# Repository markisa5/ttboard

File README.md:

# ttboard
*** test platform based on Teensy board

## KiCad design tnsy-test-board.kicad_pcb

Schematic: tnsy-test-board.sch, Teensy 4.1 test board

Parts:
C1: 4.7u; C_0603
C2: 100n; C_0603
C3, C4, C5, C6: 1u; C_0603
J1, J7: Conn_01x02; JST_EH_B02B-EH-A_02x2.50mm_Straight
J2, J3, J4: Conn_02x06_Odd_Even; JST_PUD_B12B-PUDSS_2x06x2.00mm_Straight
J5, J6, J27, J28, J29, J30, J31, J32: Conn_02x02_Odd_Even; JST_EH_B04B-EH-A_04x2.50mm_Straight
J8: Conn_02x08_Odd_Even; JST_PUD_B16B-PUDSS_2x08x2.00mm_Straight
R1, R2, R3, R4, R5, R6, R23, R33, R47, R57: 10k; R_0603
R7, R8, R9, R10, R11, R12, R13, R14, R15, R16, R17, R18, R19, R20, R21, R22, R24, R25, R26, R27, R29, R30, R31, R32, R34, R35, R36, R37, R39, R40, R41, R42, R43, R44, R45, R46, R49, R50, R51, R52, R53, R54, R55, R56, R59, R60, R61, R62, R336, R337: R; R_0603
R28, R38, R48, R58: 3.3k; R_0603
TH1, TH2, TH3, TH4: 2.2k; R_0603
U1: Teensy4.1; Teensy41
U2: ADS1015IDGS; TSSOP-10_3x3mm_Pitch0.5mm

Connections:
+5V: U1.48 (VIN); also elsewhere on the board
+24V: J7.2; also elsewhere on the board
/AO1_A0: R21.2, R22.1; also elsewhere on the board
/AO1_A1: R26.2, R27.1; also elsewhere on the board
/AO1_A2: R31.2, R32.1; also elsewhere on the board
/AO2_A0: R36.2, R37.1; also elsewhere on the board
/AO2_A1: R41.2, R42.1; also elsewhere on the board
/AO2_A2: R45.2, R46.1; also elsewhere on the board
/AO3_A0: R51.2, R52.1; also elsewhere on the board
/AO3_A1: R55.2, R56.1; also elsewhere on the board
/AO3_A2: R61.2, R62.1; also elsewhere on the board
/DI1_A0: R49.2, R50.1; also elsewhere on the board
/DI1_A1: R53.2, R54.1; also elsewhere on the board
/DI1_A2: R59.2, R60.1; also elsewhere on the board
/DIR1: U1.45 (23_A9_CRX1_MCLK1); also elsewhere on the board
/DIR2: U1.44 (22_A8_CTX1); also elsewhere on the board
/DIR3: U1.43 (21_A7_RX5_BCLK1); also elsewhere on the board
/DIR4: U1.42 (20_A6_TX5_LRCLK1); also elsewhere on the board
/DIR5: U1.37 (15_A1_RX3_SPDIF_IN); also elsewhere on the board
/DIR6: U1.36 (14_A0_TX3_SPDIF_OUT); also elsewhere on the board
/DIR7: U1.33 (41_A17); also elsewhere on the board
/DO1_A0: R19.2, R20.1; also elsewhere on the board
/DO1_A1: R24.2, R25.1; also elsewhere on the board
/DO1_A2: R29.2, R30.1; also elsewhere on the board
/DO2_A0: R34.2, R35.1; also elsewhere on the board
/DO2_A1: R39.2, R40.1; also elsewhere on the board
/DO2_A2: R43.2, R44.1; also elsewhere on the board
/DOUT1: J5.1; also elsewhere on the board
/DOUT2: J5.3; also elsewhere on the board
/DOUT3: J6.1; also elsewhere on the board
/DOUT4: J6.3; also elsewhere on the board
/DOUT5: J27.1; also elsewhere on the board
/DOUT6: J27.3; also elsewhere on the board
/DOUT7: J28.1; also elsewhere on the board
/DOUT8: J28.3; also elsewhere on the board
/DOUT9: J29.1; also elsewhere on the board
/DOUT10: J29.3; also elsewhere on the board
/DOUT11: J30.1; also elsewhere on the board
/DOUT12: J30.3; also elsewhere on the board
/DOUT13: J31.1; also elsewhere on the board
/DOUT14: J31.3; also elsewhere on the board
/DOUT15: J32.1; also elsewhere on the board
/DOUT16: J32.3; also elsewhere on the board
/DP1_A0: R9.2, R10.1; also elsewhere on the board
/DP1_A1: R7.2, R8.1; also elsewhere on the board
/DP2_A0: R13.2, R14.1; also elsewhere on the board
/DP2_A1: R11.2, R12.1; also elsewhere on the board
/DY_A0: R17.2, R18.1; also elsewhere on the board
/DY_A1: R15.2, R16.1; also elsewhere on the board
/DY_A2: R336.2, R337.1; also elsewhere on the board
/LED: U1.61 (LED); also elsewhere on the board
/MISO1: U1.14 (12_MISO_MQSL); also elsewhere on the board
/MISO2: U1.31 (39_MISO1_OUT1A); also elsewhere on the board
/MOSI1: U1.13 (11_MOSI_CTX1); also elsewhere on the board
/MOSI2: U1.18 (26_A12_MOSI1); also elsewhere on the board
/RX+: U1.60 (R+); also elsewhere on the board
/RX-: U1.65 (R-); also elsewhere on the board
/SCK1: U1.35 (13_SCK_LED); also elsewhere on the board
/SCK2: U1.19 (27_A13_SCK1); also elsewhere on the board
/SCL1: R6.2, U1.41 (19_A5_SCL); also elsewhere on the board
/SCL2: R4.2, U1.39 (17_A3_TX4_SDA1); also elsewhere on the board
/SCL3: R1.2, U1.16 (24_A10_TX6_SCL2), U2.9 (SDA)
/SDA1: R5.2, U1.40 (18_A4_SDA); also elsewhere on the board
/SDA2: R3.2, U1.38 (16_A2_RX4_SCL1); also elsewhere on the board
/SDA3: R2.2, U1.17 (25_A11_RX6_SDA2), U2.10 (SCL)
/T1: C3.1, R23.2, U2.4 (AIN0)
/T1A: J4.1; also elsewhere on the board
/T1B: J4.2; also elsewhere on the board
/T2: C4.1, R33.2, U2.5 (AIN1)
/T2A: J4.3; also elsewhere on the board
/T2B: J4.4; also elsewhere on the board
/T3: C5.1, R47.2, U2.6 (AIN2)
/T3A: J4.5; also elsewhere on the board
/T3B: J4.6; also elsewhere on the board
/T4: C6.1, R57.2, U2.7 (AIN3)
/T4A: J4.7; also elsewhere on the board
/T4B: J4.8; also elsewhere on the board
/T5A: J4.9; also elsewhere on the board
/T5B: J4.10; also elsewhere on the board
/T6A: J4.11; also elsewhere on the board
/T6B: J4.12; also elsewhere on the board
/TX+: U1.63 (T+); also elsewhere on the board
/TX-: U1.62 (T-); also elsewhere on the board
/VBAT: U1.50 (VBAT)
/VUSB: U1.49 (VUSB)
/analog-inputs-1/G1: J2.1; also elsewhere on the board
/analog-inputs-1/G2: J2.3; also elsewhere on the board
/analog-inputs-1/G3: J2.5; also elsewhere on the board
/analog-inputs-1/G4: J2.7; also elsewhere on the board
/analog-inputs-1/G5: J2.9; also elsewhere on the board
/analog-inputs-1/G6: J2.11; also elsewhere on the board
/analog-inputs-2/G1: J3.1; also elsewhere on the board
/analog-inputs-2/G2: J3.3; also elsewhere on the board
/analog-inputs-2/G3: J3.5; also elsewhere on the board
/analog-inputs-2/G4: J3.7; also elsewhere on the board
/analog-inputs-2/G5: J3.9; also elsewhere on the board
/analog-inputs-2/G6: J3.11; also elsewhere on the board
/digital-inputs/DIN1: J8.1; also elsewhere on the board
/digital-inputs/DIN2: J8.3; also elsewhere on the board
/digital-inputs/DIN3: J8.5; also elsewhere on the board
/digital-inputs/DIN4: J8.7; also elsewhere on the board
/digital-inputs/DIN5: J8.9; also elsewhere on the board
/digital-inputs/DIN6: J8.11; also elsewhere on the board
/digital-inputs/DIN7: J8.13; also elsewhere on the board
/digital-inputs/DIN8: J8.15; also elsewhere on the board
/~CS1~: U1.12 (10_CS_MQSR); also elsewhere on the board
/~CS2~: U1.30 (38_CS1_IN1); also elsewhere on the board
GND: C1.2, C2.2, C3.2, C4.2, C5.2, C6.2, J2.2, J2.4, J2.6, J2.8, J2.10, J2.12, J3.2, J3.4, J3.6, J3.8, J3.10, J3.12, J5.2, J5.4, J6.2, J6.4, J8.2, J8.4, J8.6, J8.8, J8.10, J8.12, J8.14, J8.16, J27.2, J27.4, J28.2, J28.4, J29.2, J29.4, J30.2, J30.4, J31.2, J31.4, J32.2, J32.4, R8.2, R10.2, R12.2, R14.2, R16.2, R18.2, R20.2, R22.2, R25.2, R27.2, R30.2, R32.2, R35.2, R37.2, R40.2, R42.2, R44.2, R46.2, R50.2, R52.2, R54.2, R56.2, R60.2, R62.2, R337.2, TH1.2, TH2.2, TH3.2, TH4.2, U1.1 (GND), U1.34 (GND), U1.47 (GND), U1.52 (GND), U1.64 (GND), U2.1 (ADDR), U2.3 (GND); also elsewhere on the board
GNDPWR: J1.1, J7.1; also elsewhere on the board
unnamed: R23.1, R28.2, TH1.1
unnamed: R33.1, R38.2, TH2.1
unnamed: R47.1, R48.2, TH3.1
unnamed: R57.1, R58.2, TH4.1
VDC: J1.2

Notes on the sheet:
ONBOARD TEMPERATURE
+ simulate gate source caps
+24V@3A
I2C
POTI SIMULATE TEMPERATURES x3 CHANNELS
8x DIGITAL OUTPUTS
OnBoard Display Device
SPI
ETHERNET EXTENSION BOARD
DIGITAL OUTPUTS
DIGITAL POTENTIOMETERS
ANALOG OUTPUTS
DISPLAY INTERFACE
POWER SUPPLY
ETHERNET EXPANSION
ANALOG INPUTS
DIGITAL INPUTS
I2C 3-bit address (3 devices)
I2C 3-bit address (2 devices)
I2C 2-bit address (2 devices)
SPI - 2 devices
I2C 2-bit address (1 device)
I2C 3-bit address (1 device)
8x ANALOG OUTPUTS
6x ANALOG INPUTS
8x DIGITAL INPUTS
I2C BUS 1
I2C BUS 2
6 SPARE
ADDRESS SELECTOR
DIGITAL POTI 1
DIGITAL POTI 2
DIGITAL OUT 1
DIGITAL OUT 2
DIGITAL IN 1
ANALOG OUT 1
ANALOG OUT 2
ANALOG OUT 3
DISPLAY
LEM current simulation

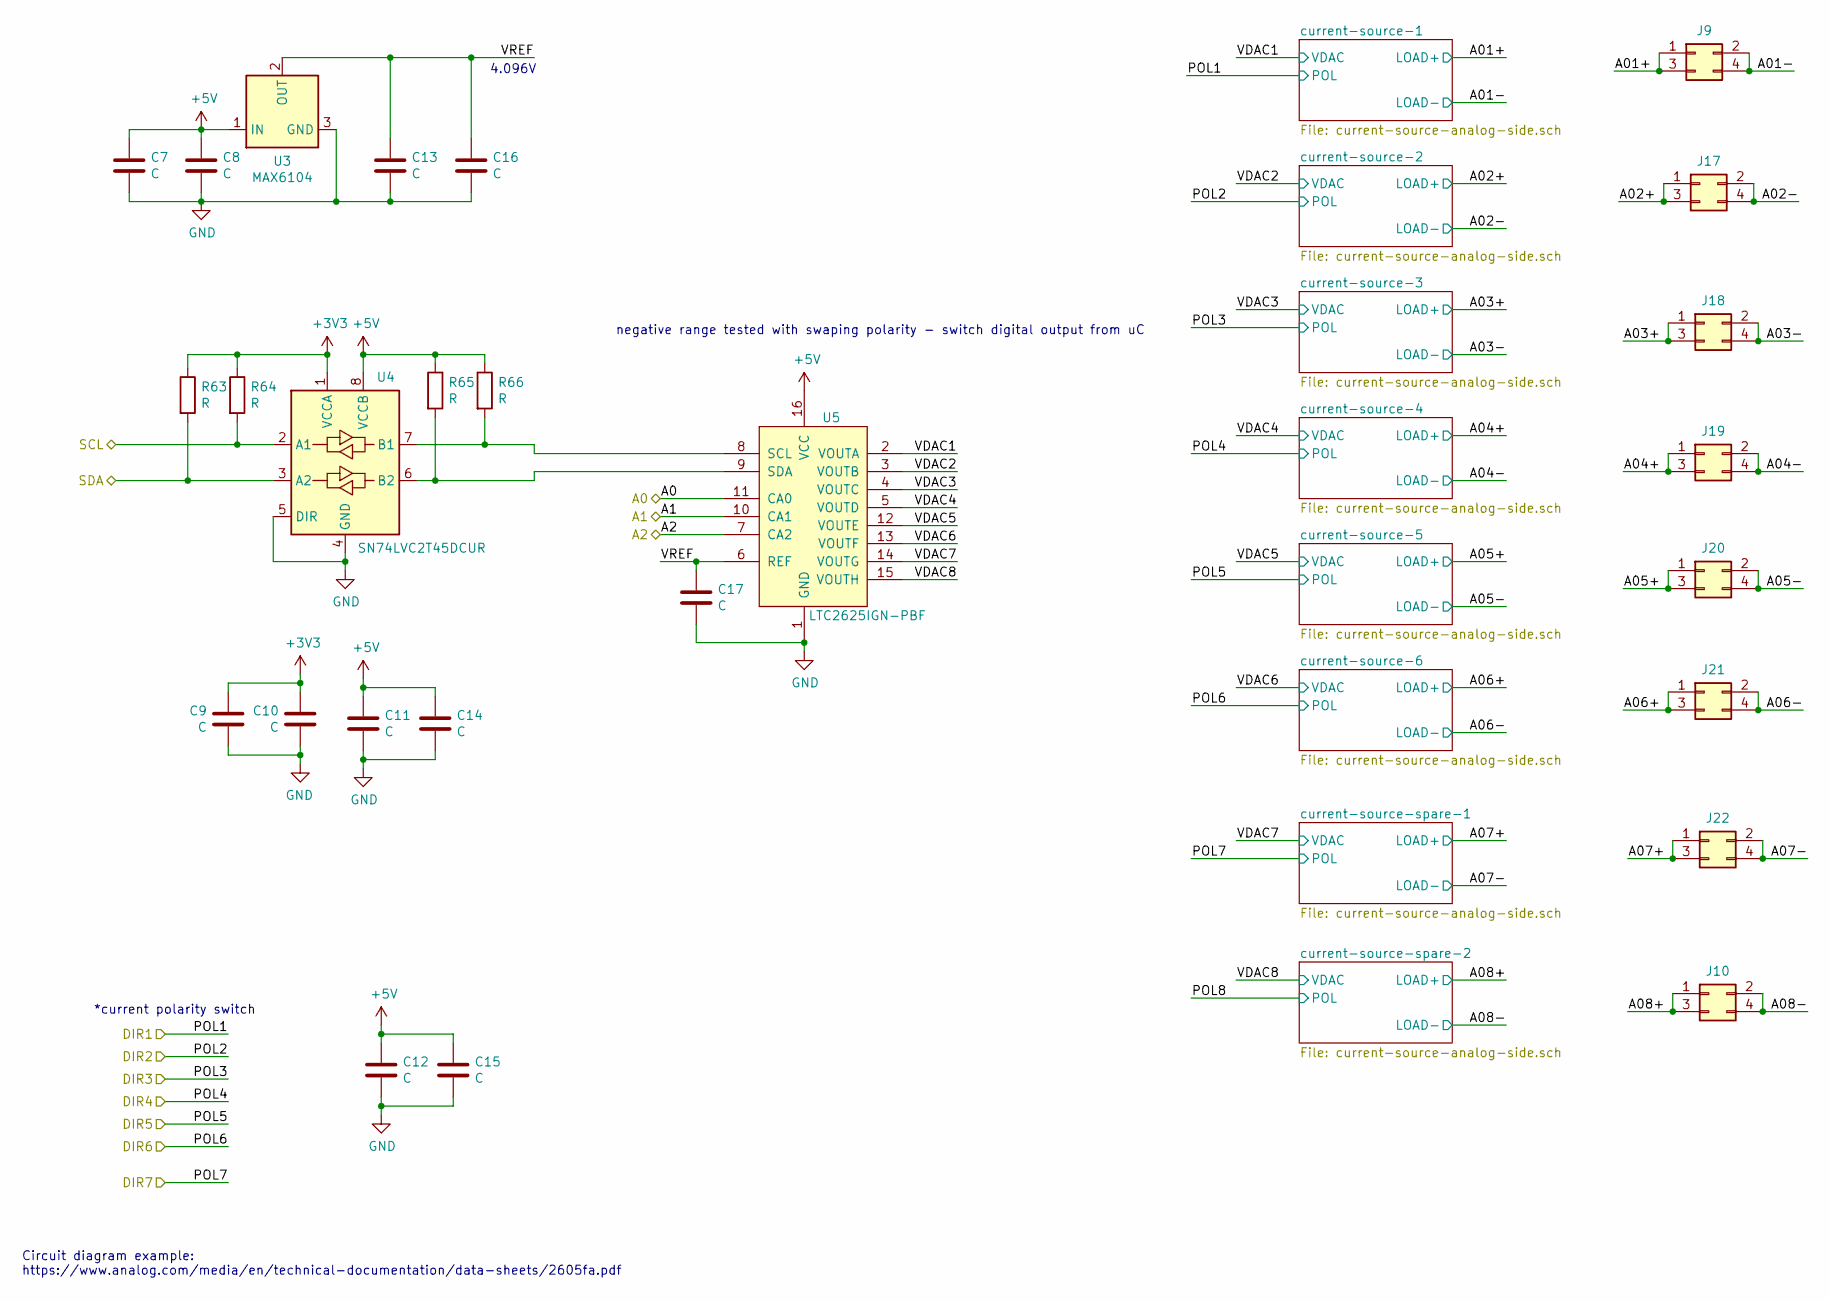
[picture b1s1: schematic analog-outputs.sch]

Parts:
C7, C8, C9, C10, C11, C12, C13, C14, C15, C16, C17: C; C_0603
J9, J10, J17, J18, J19, J20, J21, J22: Conn_02x02_Odd_Even; JST_EH_B04B-EH-A_04x2.50mm_Straight
R63, R64, R65, R66: R; R_0603
U3: MAX6104; SOT-23
U4: SN74LVC2T45DCUR; VSSOP-8_2.3x2mm_Pitch0.5mm
U5: LTC2625IGN-PBF; SSOP-16_3.9x4.9mm_Pitch0.635mm

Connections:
+5V: C7.1, C8.1, C11.1, C12.1, C14.1, C15.1, R65.1, R66.1, U3.1 (IN), U4.8 (VCCB), U5.16 (VCC); also elsewhere on the board
/AO1_A0: U5.11 (CA0); also elsewhere on the board
/AO1_A1: U5.10 (CA1); also elsewhere on the board
/AO1_A2: U5.7 (CA2); also elsewhere on the board
/SCL2: R63.2, U4.3 (A2); also elsewhere on the board
/SDA2: R64.2, U4.2 (A1); also elsewhere on the board
/analog-outputs-1/A01+: J9.1, J9.3; also elsewhere on the board
/analog-outputs-1/A01-: J9.2, J9.4; also elsewhere on the board
/analog-outputs-1/A02+: J17.1, J17.3; also elsewhere on the board
/analog-outputs-1/A02-: J17.2, J17.4; also elsewhere on the board
/analog-outputs-1/A03+: J18.1, J18.3; also elsewhere on the board
/analog-outputs-1/A03-: J18.2, J18.4; also elsewhere on the board
/analog-outputs-1/A04+: J19.1, J19.3; also elsewhere on the board
/analog-outputs-1/A04-: J19.2, J19.4; also elsewhere on the board
/analog-outputs-1/A05+: J20.1, J20.3; also elsewhere on the board
/analog-outputs-1/A05-: J20.2, J20.4; also elsewhere on the board
/analog-outputs-1/A06+: J21.1, J21.3; also elsewhere on the board
/analog-outputs-1/A06-: J21.2, J21.4; also elsewhere on the board
/analog-outputs-1/A07+: J22.1, J22.3; also elsewhere on the board
/analog-outputs-1/A07-: J22.2, J22.4; also elsewhere on the board
/analog-outputs-1/A08+: J10.1, J10.3; also elsewhere on the board
/analog-outputs-1/A08-: J10.2, J10.4; also elsewhere on the board
/analog-outputs-1/VDAC1: U5.2 (VOUTA); also elsewhere on the board
/analog-outputs-1/VDAC2: U5.3 (VOUTB); also elsewhere on the board
/analog-outputs-1/VDAC3: U5.4 (VOUTC); also elsewhere on the board
/analog-outputs-1/VDAC4: U5.5 (VOUTD); also elsewhere on the board
/analog-outputs-1/VDAC5: U5.12 (VOUTE); also elsewhere on the board
/analog-outputs-1/VDAC6: U5.13 (VOUTF); also elsewhere on the board
/analog-outputs-1/VDAC7: U5.14 (VOUTG); also elsewhere on the board
/analog-outputs-1/VDAC8: U5.15 (VOUTH); also elsewhere on the board
/analog-outputs-1/VREF: C13.1, C16.1, C17.1, U3.2 (OUT), U5.6 (REF)
GND: C7.2, C8.2, C9.2, C10.2, C11.2, C12.2, C13.2, C14.2, C15.2, C16.2, C17.2, U3.3 (GND), U4.4 (GND), U4.5 (DIR), U5.1 (GND); also elsewhere on the board
unnamed: R65.2, U4.6 (B2), U5.9 (SDA)
unnamed: R66.2, U4.7 (B1), U5.8 (SCL)

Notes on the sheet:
Circuit diagram example: https://www.analog.com/media/en/technical-documentation/data-sheets/2605fa.pdf
negative range tested with swaping polarity - switch digital output from uC
*current polarity switch
4.096V

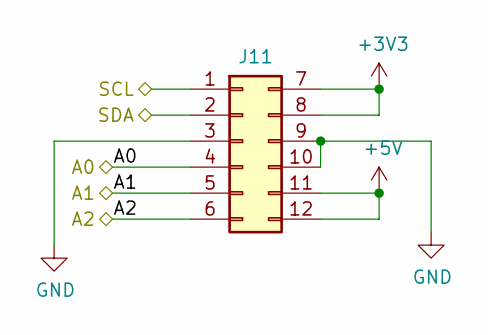
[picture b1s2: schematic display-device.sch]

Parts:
J11: Conn_02x06_Top_Bottom; JST_PUD_B12B-PUDSS_2x06x2.00mm_Straight

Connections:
+5V: J11.11, J11.12; also elsewhere on the board
/DY_A0: J11.4; also elsewhere on the board
/DY_A1: J11.5; also elsewhere on the board
/DY_A2: J11.6; also elsewhere on the board
/SCL1: J11.1; also elsewhere on the board
/SDA1: J11.2; also elsewhere on the board
GND: J11.3, J11.9, J11.10; also elsewhere on the board

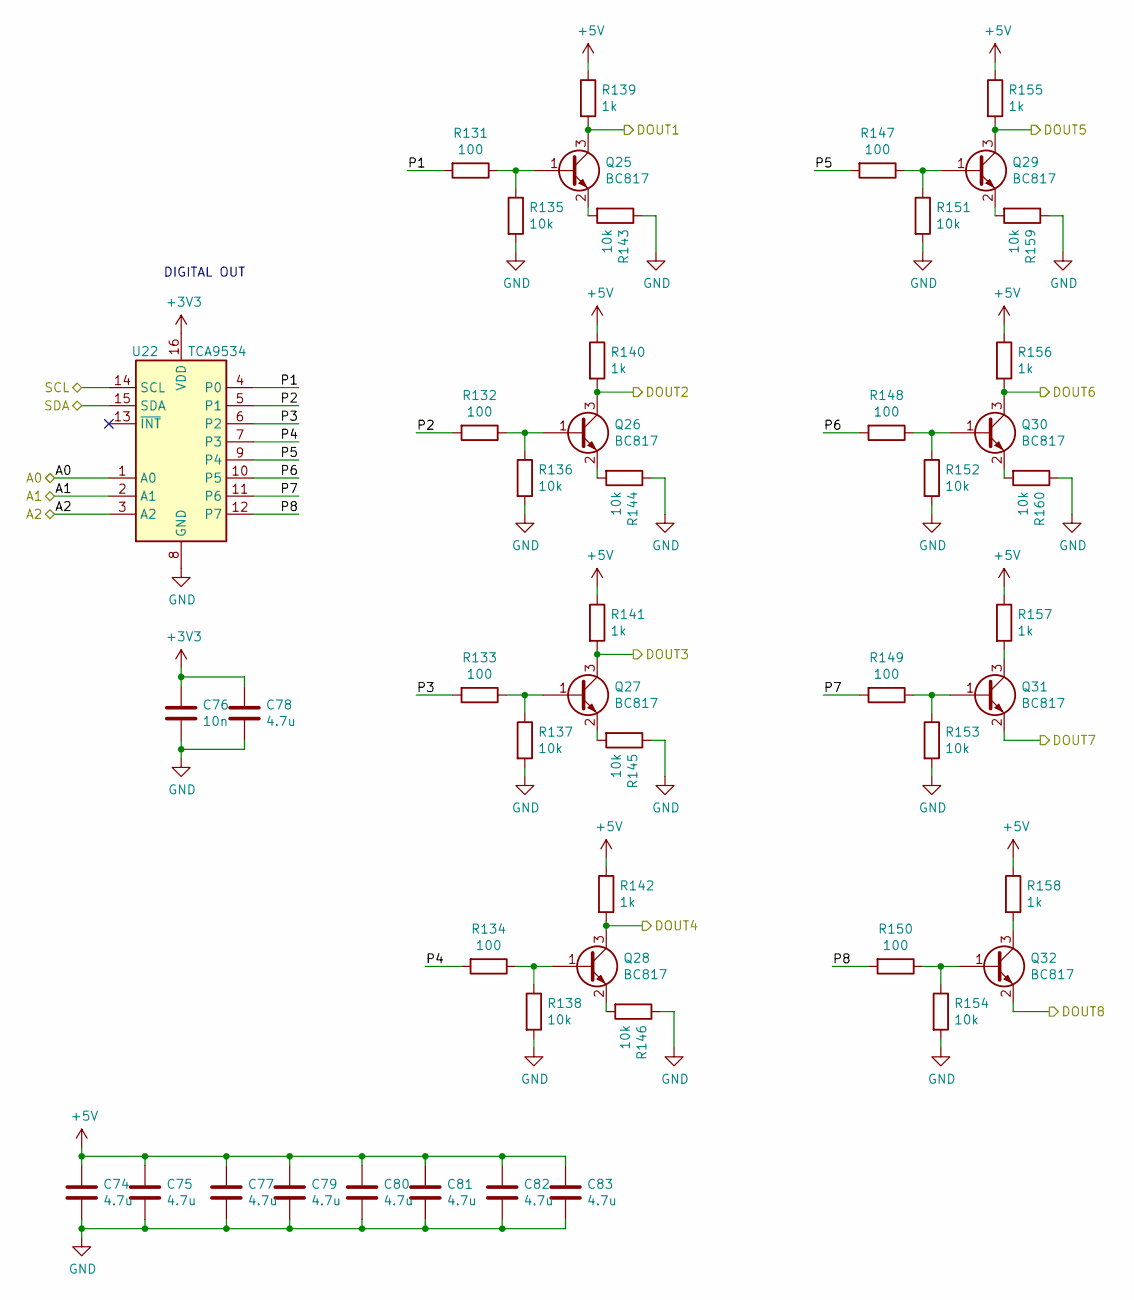
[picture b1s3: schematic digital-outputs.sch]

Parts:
C74, C75, C77, C78, C79, C80, C81, C82, C83: 4.7u; C_0603
C76: 10n; C_0603
Q25, Q26, Q27, Q28, Q29, Q30, Q31, Q32: BC817; SOT-23
R131, R132, R133, R134, R147, R148, R149, R150: 100; R_0603
R135, R136, R137, R138, R143, R144, R145, R146, R151, R152, R153, R154, R159, R160: 10k; R_0603
R139, R140, R141, R142, R155, R156, R157, R158: 1k; R_0603
U22: TCA9534; TSSOP-16_4.4x5mm_Pitch0.65mm

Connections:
+5V: C74.1, C75.1, C77.1, C79.1, C80.1, C81.1, C82.1, C83.1, R139.1, R140.1, R141.1, R142.1, R155.1, R156.1, R157.1, R158.1; also elsewhere on the board
/DO1_A0: U22.1 (A0); also elsewhere on the board
/DO1_A1: U22.2 (A1); also elsewhere on the board
/DO1_A2: U22.3 (A2); also elsewhere on the board
/DOUT1: Q25.3 (C), R139.2; also elsewhere on the board
/DOUT2: Q26.3 (C), R140.2; also elsewhere on the board
/DOUT3: Q27.3 (C), R141.2; also elsewhere on the board
/DOUT4: Q28.3 (C), R142.2; also elsewhere on the board
/DOUT5: Q29.3 (C), R155.2; also elsewhere on the board
/DOUT6: Q30.3 (C), R156.2; also elsewhere on the board
/DOUT7: Q31.2 (E); also elsewhere on the board
/DOUT8: Q32.2 (E); also elsewhere on the board
/SCL2: U22.14 (SCL); also elsewhere on the board
/SDA2: U22.15 (SDA); also elsewhere on the board
/digital-outputs-1/P1: R131.2, U22.4 (P0)
/digital-outputs-1/P2: R132.2, U22.5 (P1)
/digital-outputs-1/P3: R133.2, U22.6 (P2)
/digital-outputs-1/P4: R134.2, U22.7 (P3)
/digital-outputs-1/P5: R147.2, U22.9 (P4)
/digital-outputs-1/P6: R148.2, U22.10 (P5)
/digital-outputs-1/P7: R149.2, U22.11 (P6)
/digital-outputs-1/P8: R150.2, U22.12 (P7)
GND: C74.2, C75.2, C76.2, C77.2, C78.2, C79.2, C80.2, C81.2, C82.2, C83.2, R135.2, R136.2, R137.2, R138.2, R143.1, R144.1, R145.1, R146.1, R151.2, R152.2, R153.2, R154.2, R159.1, R160.1, U22.8 (GND); also elsewhere on the board
unnamed: Q25.1 (B), R131.1, R135.1
unnamed: Q25.2 (E), R143.2
unnamed: Q26.1 (B), R132.1, R136.1
unnamed: Q26.2 (E), R144.2
unnamed: Q27.1 (B), R133.1, R137.1
unnamed: Q27.2 (E), R145.2
unnamed: Q28.1 (B), R134.1, R138.1
unnamed: Q28.2 (E), R146.2
unnamed: Q29.1 (B), R147.1, R151.1
unnamed: Q29.2 (E), R159.2
unnamed: Q30.1 (B), R148.1, R152.1
unnamed: Q30.2 (E), R160.2
unnamed: Q31.1 (B), R149.1, R153.1
unnamed: Q31.3 (C), R157.2
unnamed: Q32.1 (B), R150.1, R154.1
unnamed: Q32.3 (C), R158.2

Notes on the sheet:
DIGITAL OUT

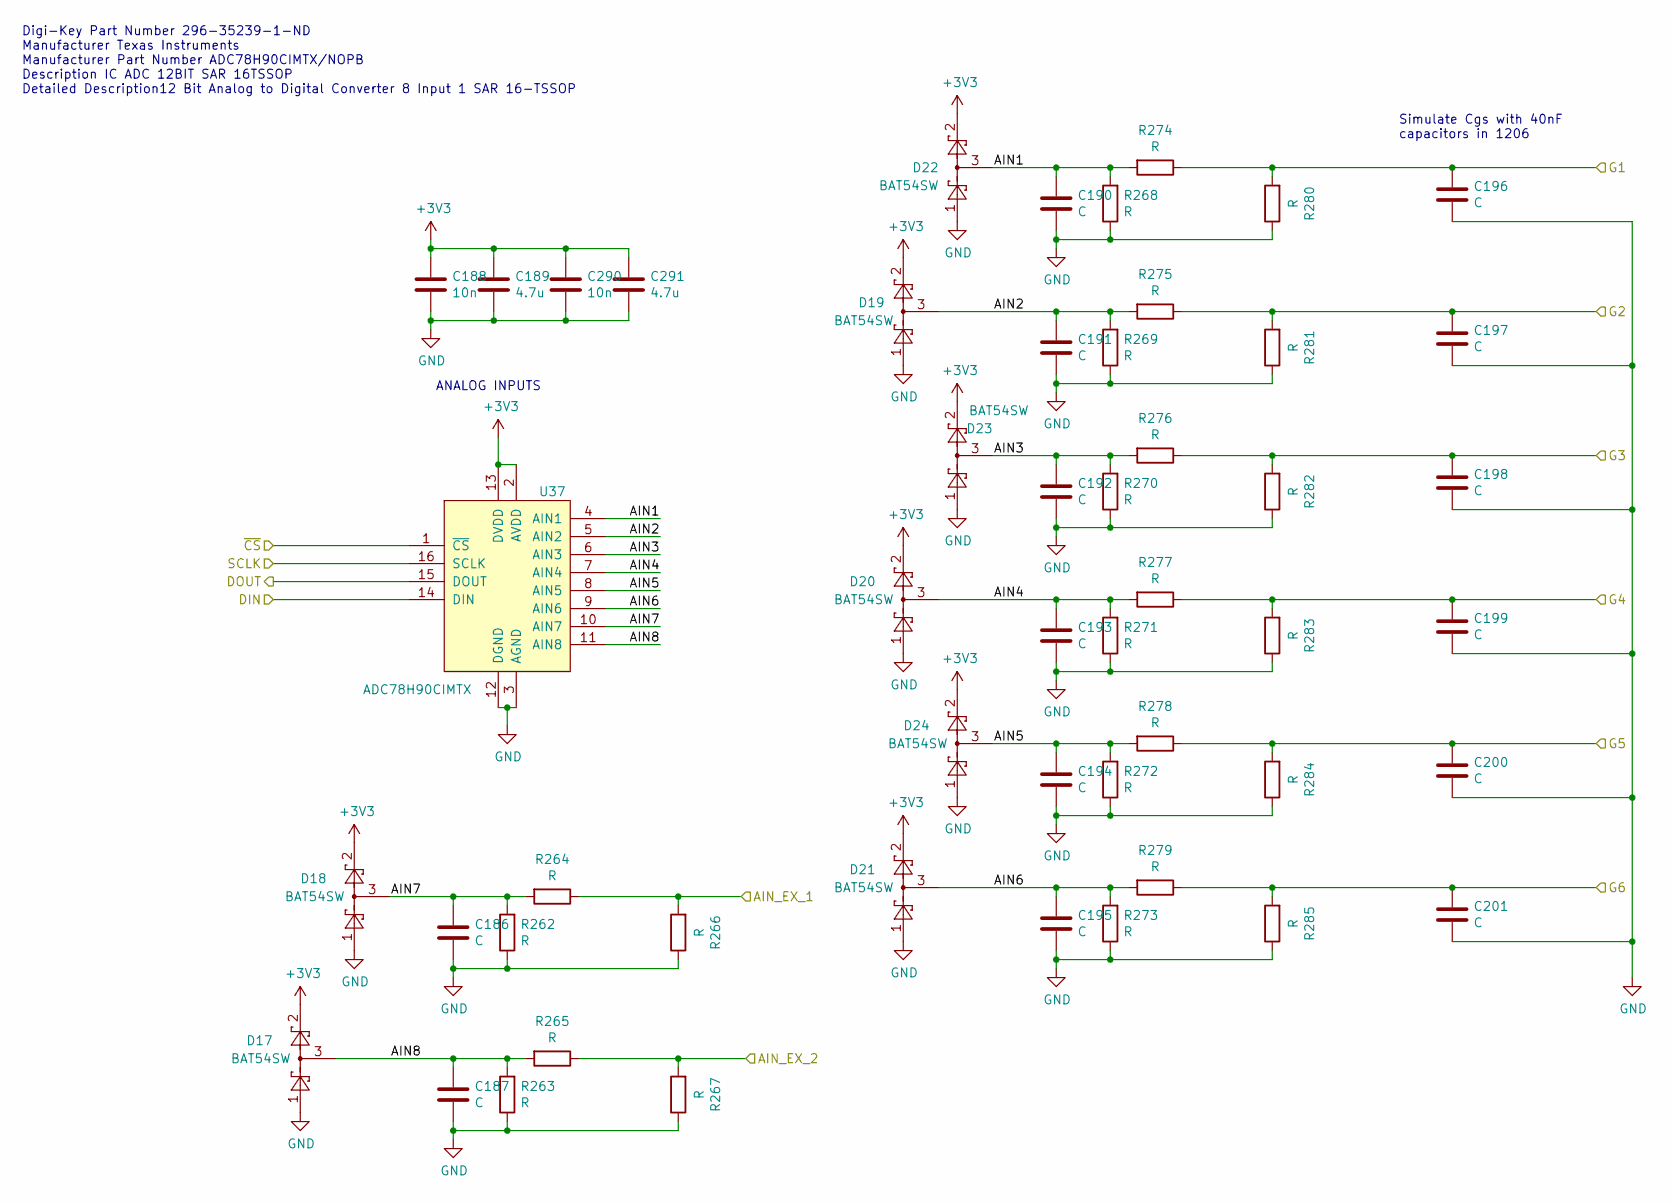
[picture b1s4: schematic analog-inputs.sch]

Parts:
C86, C288: 10n; C_0603
C87, C289: 4.7u; C_0603
C186, C187, C190, C191, C192, C193, C194, C195: C; C_0603
C196, C197, C198, C199, C200, C201: C; C_1206
D1, D2, D3, D4, D5, D6, D7, D8: BAT54SW; SOT-323_SC-70_Handsoldering
R262, R263, R264, R265, R268, R269, R270, R271, R272, R273, R274, R275, R276, R277, R278, R279: R; R_0603
R266, R267, R280, R281, R282, R283, R284, R285: R; R_0805
U37: ADC78H90CIMTX; TSSOP-16_4.4x5mm_Pitch0.65mm

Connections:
/AIN_3V3: R264.1, R266.2
/AIN_5V: R265.1, R267.2
/MISO1: U37.15 (DOUT); also elsewhere on the board
/MOSI1: U37.14 (DIN); also elsewhere on the board
/SCK1: U37.16 (SCLK); also elsewhere on the board
/analog-inputs-1/G1: C196.1, R274.1, R280.2; also elsewhere on the board
/analog-inputs-1/G2: C197.1, R275.1, R281.2; also elsewhere on the board
/analog-inputs-1/G3: C198.1, R276.1, R282.2; also elsewhere on the board
/analog-inputs-1/G4: C199.1, R277.1, R283.2; also elsewhere on the board
/analog-inputs-1/G5: C200.1, R278.1, R284.2; also elsewhere on the board
/analog-inputs-1/G6: C201.1, R279.1, R285.2; also elsewhere on the board
/~CS1~: U37.1 (~CS~); also elsewhere on the board
GND: C86.2, C87.2, C186.2, C187.2, C190.2, C191.2, C192.2, C193.2, C194.2, C195.2, C196.2, C197.2, C198.2, C199.2, C200.2, C201.2, C288.2, C289.2, D1.1, D2.1, D3.1, D4.1, D5.1, D6.1, D7.1, D8.1, R262.1, R263.1, R266.1, R267.1, R268.1, R269.1, R270.1, R271.1, R272.1, R273.1, R280.1, R281.1, R282.1, R283.1, R284.1, R285.1, U37.3 (AGND), U37.12 (DGND); also elsewhere on the board

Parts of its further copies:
C84, C85, C88, C89, C90, C91, C92, C93: C; C_0603
C94, C95, C96, C97, C98, C99: C; C_1206
C188, C290: 10n; C_0603
C189, C291: 4.7u; C_0603
D17, D18, D19, D20, D21, D22, D23, D24: BAT54SW; SOT-323_SC-70_Handsoldering
R161, R162, R163, R164, R167, R168, R169, R170, R171, R172, R173, R174, R175, R176, R177, R178: R; R_0603
R165, R166, R179, R180, R181, R182, R183, R184: R; R_0805
U23: ADC78H90CIMTX; TSSOP-16_4.4x5mm_Pitch0.65mm

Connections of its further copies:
/AIN_12V: R163.1, R165.2
/AIN_24V: R164.1, R166.2
/MISO2: U23.15 (DOUT); also elsewhere on the board
/MOSI2: U23.14 (DIN); also elsewhere on the board
/SCK2: U23.16 (SCLK); also elsewhere on the board
/analog-inputs-2/G1: C94.1, R173.1, R179.2; also elsewhere on the board
/analog-inputs-2/G2: C95.1, R174.1, R180.2; also elsewhere on the board
/analog-inputs-2/G3: C96.1, R175.1, R181.2; also elsewhere on the board
/analog-inputs-2/G4: C97.1, R176.1, R182.2; also elsewhere on the board
/analog-inputs-2/G5: C98.1, R177.1, R183.2; also elsewhere on the board
/analog-inputs-2/G6: C99.1, R178.1, R184.2; also elsewhere on the board
/~CS2~: U23.1 (~CS~); also elsewhere on the board
GND: C84.2, C85.2, C88.2, C89.2, C90.2, C91.2, C92.2, C93.2, C94.2, C95.2, C96.2, C97.2, C98.2, C99.2, C188.2, C189.2, C290.2, C291.2, D17.1, D18.1, D19.1, D20.1, D21.1, D22.1, D23.1, D24.1, R161.1, R162.1, R165.1, R166.1, R167.1, R168.1, R169.1, R170.1, R171.1, R172.1, R179.1, R180.1, R181.1, R182.1, R183.1, R184.1, U23.3 (AGND), U23.12 (DGND); also elsewhere on the board

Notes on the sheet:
ANALOG INPUTS
Digi-Key Part Number 296-35239-1-ND Manufacturer Texas Instruments Manufacturer Part Number ADC78H90CIMTX/NOPB Description IC ADC 12BIT SAR 16TSSOP Detailed Description12 Bit Analog to Digital Converter 8 Input 1 SAR 16-TSSOP
Simulate Cgs with 40nF capacitors in 1206

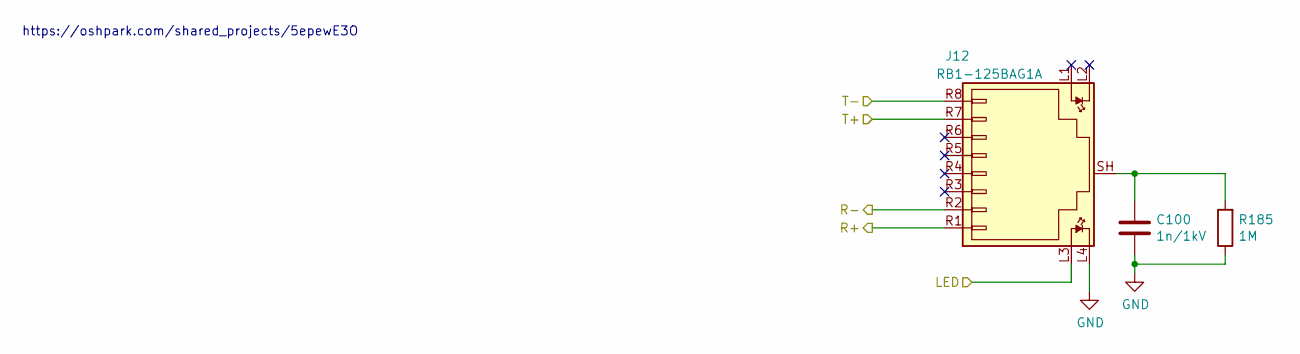
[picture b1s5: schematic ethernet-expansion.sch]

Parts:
C100: 1n/1kV; C_0603
J12: RB1-125BAG1A; RJ45_Female_RB1-125BAG1A; MPN RB1-125BAG1A; Digi-Key_PN 1278-1011-ND
R185: 1M; R_0805

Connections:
/LED: J12.L3; also elsewhere on the board
/RX+: J12.R1; also elsewhere on the board
/RX-: J12.R2; also elsewhere on the board
/TX+: J12.R7; also elsewhere on the board
/TX-: J12.R8; also elsewhere on the board
GND: C100.2, J12.L4, R185.1; also elsewhere on the board
unnamed: C100.1, J12.SH, R185.2

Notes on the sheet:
https://oshpark.com/shared_projects/5epewE3O

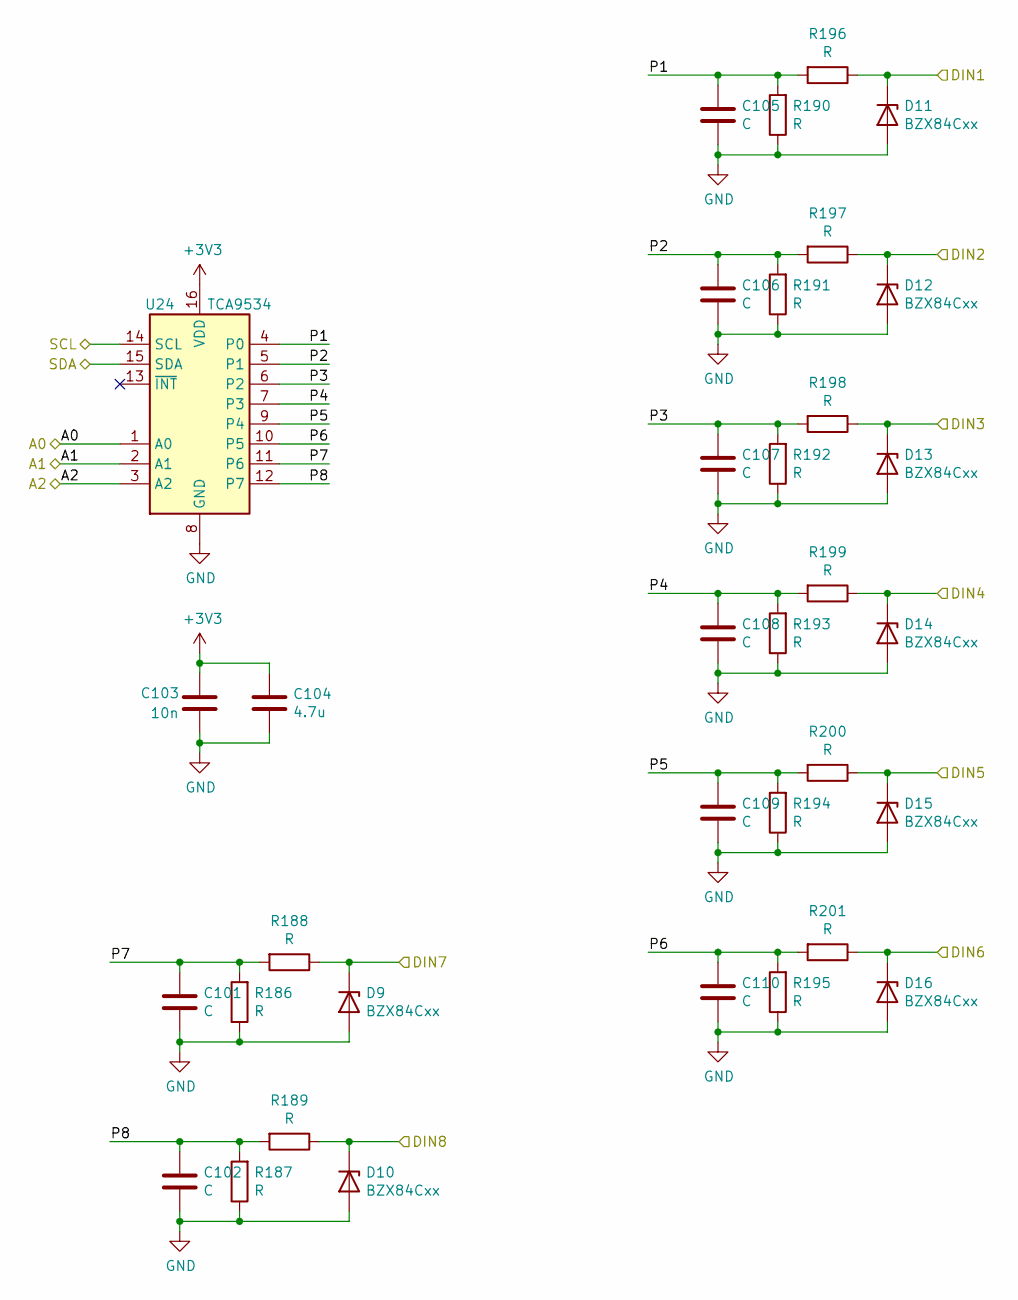
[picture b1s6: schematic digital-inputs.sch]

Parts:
C101, C102, C105, C106, C107, C108, C109, C110: C; C_0603
C103: 10n; C_0603
C104: 4.7u; C_0603
D9, D10, D11, D12, D13, D14, D15, D16: BZX84Cxx; D_SOT-23_ANK
R186, R187, R188, R189, R190, R191, R192, R193, R194, R195, R196, R197, R198, R199, R200, R201: R; R_0603
U24: TCA9534; TSSOP-16_4.4x5mm_Pitch0.65mm

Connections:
/DI1_A0: U24.1 (A0); also elsewhere on the board
/DI1_A1: U24.2 (A1); also elsewhere on the board
/DI1_A2: U24.3 (A2); also elsewhere on the board
/SCL2: U24.14 (SCL); also elsewhere on the board
/SDA2: U24.15 (SDA); also elsewhere on the board
/digital-inputs/DIN1: D11.1 (K), R196.1; also elsewhere on the board
/digital-inputs/DIN2: D12.1 (K), R197.1; also elsewhere on the board
/digital-inputs/DIN3: D13.1 (K), R198.1; also elsewhere on the board
/digital-inputs/DIN4: D14.1 (K), R199.1; also elsewhere on the board
/digital-inputs/DIN5: D15.1 (K), R200.1; also elsewhere on the board
/digital-inputs/DIN6: D16.1 (K), R201.1; also elsewhere on the board
/digital-inputs/DIN7: D9.1 (K), R188.1; also elsewhere on the board
/digital-inputs/DIN8: D10.1 (K), R189.1; also elsewhere on the board
/digital-inputs/P1: C105.1, R190.2, R196.2, U24.4 (P0)
/digital-inputs/P2: C106.1, R191.2, R197.2, U24.5 (P1)
/digital-inputs/P3: C107.1, R192.2, R198.2, U24.6 (P2)
/digital-inputs/P4: C108.1, R193.2, R199.2, U24.7 (P3)
/digital-inputs/P5: C109.1, R194.2, R200.2, U24.9 (P4)
/digital-inputs/P6: C110.1, R195.2, R201.2, U24.10 (P5)
/digital-inputs/P7: C101.1, R186.2, R188.2, U24.11 (P6)
/digital-inputs/P8: C102.1, R187.2, R189.2, U24.12 (P7)
GND: C101.2, C102.2, C103.2, C104.2, C105.2, C106.2, C107.2, C108.2, C109.2, C110.2, D9.2 (A), D10.2 (A), D11.2 (A), D12.2 (A), D13.2 (A), D14.2 (A), D15.2 (A), D16.2 (A), R186.1, R187.1, R190.1, R191.1, R192.1, R193.1, R194.1, R195.1, U24.8 (GND); also elsewhere on the board

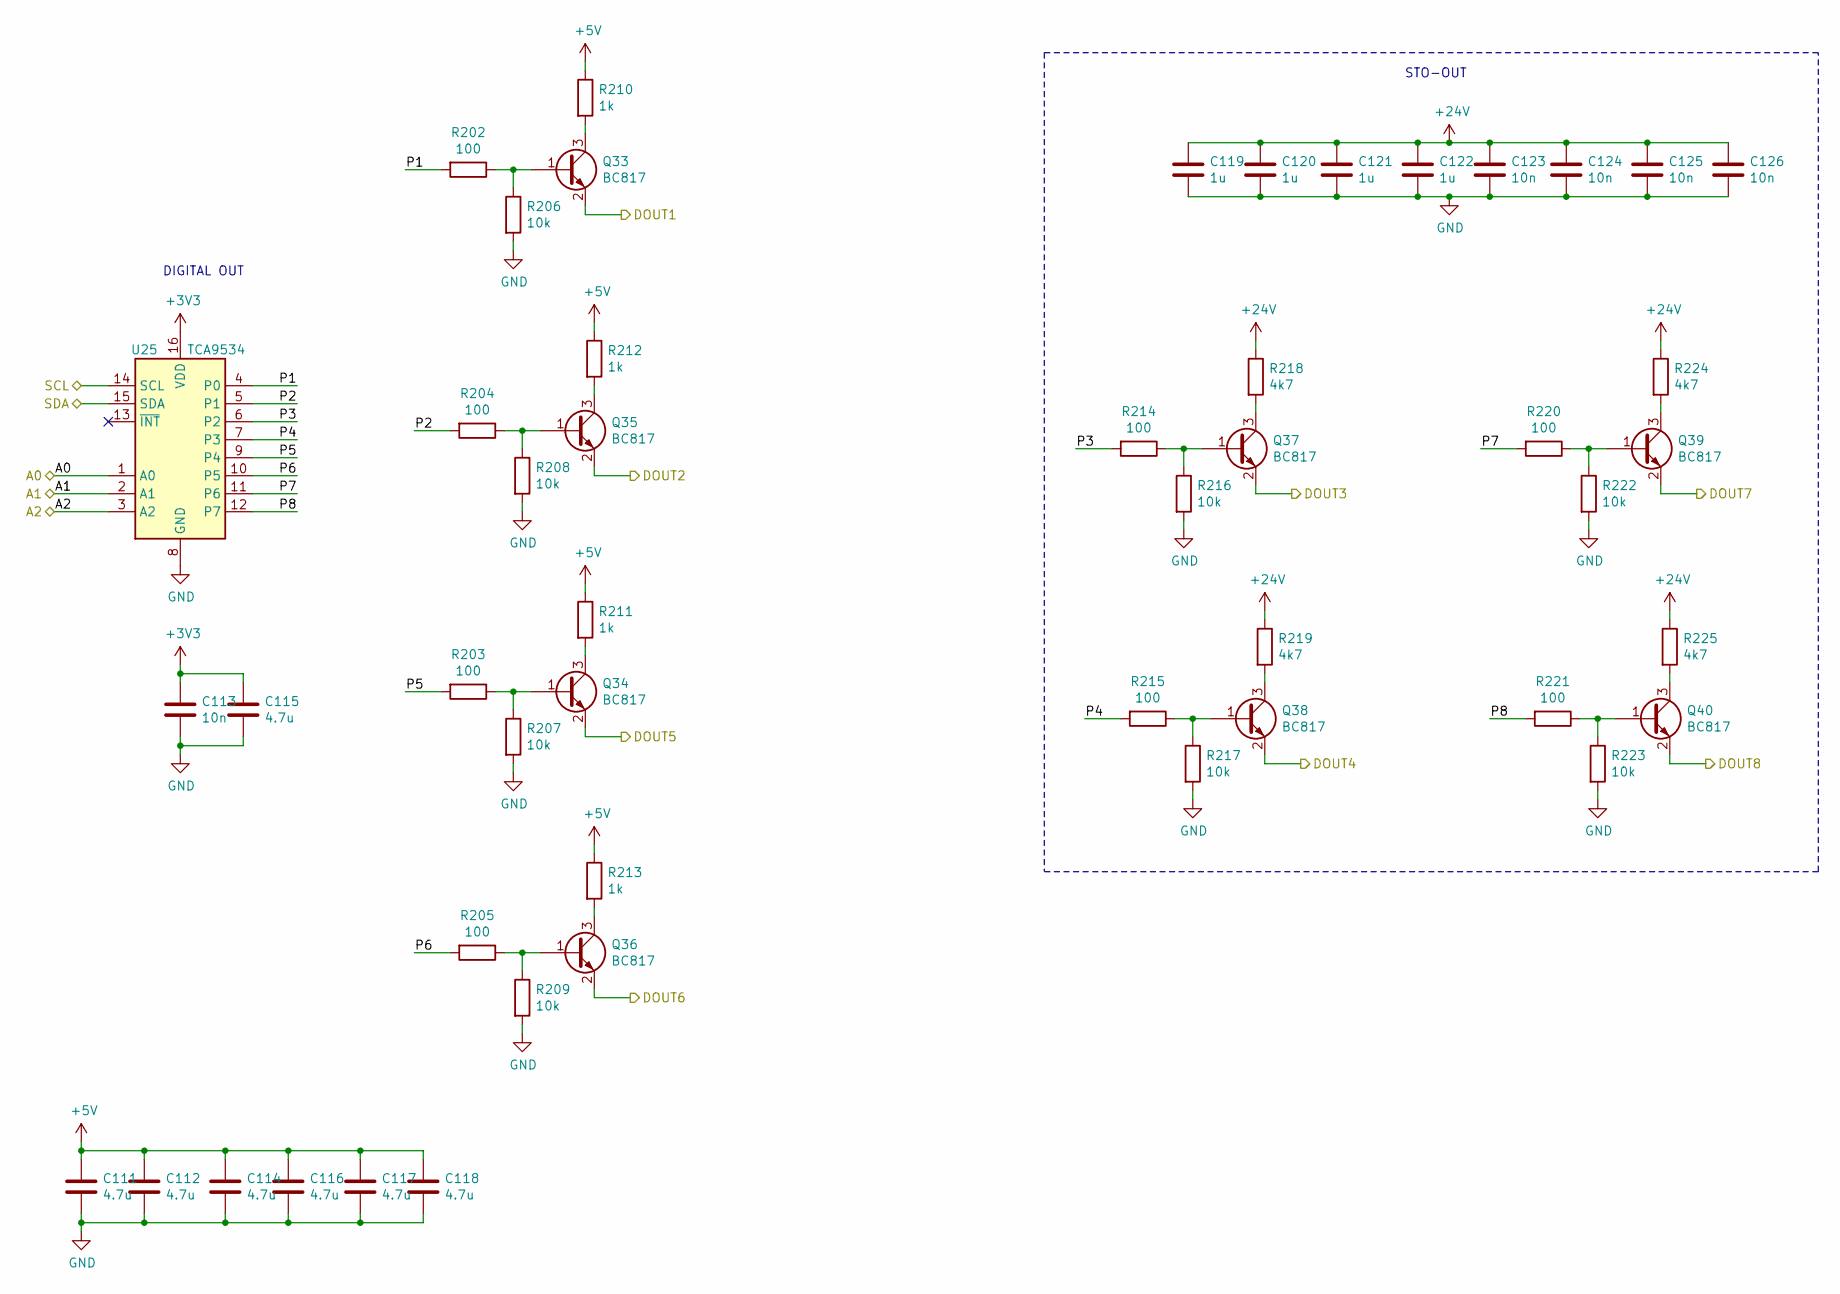
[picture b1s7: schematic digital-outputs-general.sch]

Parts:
C111, C112, C114, C115, C116, C117, C118: 4.7u; C_0603
C113, C123, C124, C125, C126: 10n; C_0603
C119, C120, C121, C122: 1u; C_0603
Q33, Q34, Q35, Q36, Q37, Q38, Q39, Q40: BC817; SOT-23
R202, R203, R204, R205, R214, R215, R220, R221: 100; R_0603
R206, R207, R208, R209, R216, R217, R222, R223: 10k; R_0603
R210, R211, R212, R213: 1k; R_0603
R218, R219, R224, R225: 4k7; R_0603
U25: TCA9534; TSSOP-16_4.4x5mm_Pitch0.65mm

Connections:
+5V: C111.1, C112.1, C114.1, C116.1, C117.1, C118.1, R210.1, R211.1, R212.1, R213.1; also elsewhere on the board
+24V: C119.1, C120.1, C121.1, C122.1, C123.1, C124.1, C125.1, C126.1, R218.1, R219.1, R224.1, R225.1; also elsewhere on the board
/DO2_A0: U25.1 (A0); also elsewhere on the board
/DO2_A1: U25.2 (A1); also elsewhere on the board
/DO2_A2: U25.3 (A2); also elsewhere on the board
/DOUT9: Q33.2 (E); also elsewhere on the board
/DOUT10: Q35.2 (E); also elsewhere on the board
/DOUT11: Q37.2 (E); also elsewhere on the board
/DOUT12: Q38.2 (E); also elsewhere on the board
/DOUT13: Q34.2 (E); also elsewhere on the board
/DOUT14: Q36.2 (E); also elsewhere on the board
/DOUT15: Q39.2 (E); also elsewhere on the board
/DOUT16: Q40.2 (E); also elsewhere on the board
/SCL2: U25.14 (SCL); also elsewhere on the board
/SDA2: U25.15 (SDA); also elsewhere on the board
/digital-outputs-2/P1: R202.2, U25.4 (P0)
/digital-outputs-2/P2: R204.2, U25.5 (P1)
/digital-outputs-2/P3: R214.2, U25.6 (P2)
/digital-outputs-2/P4: R215.2, U25.7 (P3)
/digital-outputs-2/P5: R203.2, U25.9 (P4)
/digital-outputs-2/P6: R205.2, U25.10 (P5)
/digital-outputs-2/P7: R220.2, U25.11 (P6)
/digital-outputs-2/P8: R221.2, U25.12 (P7)
GND: C111.2, C112.2, C113.2, C114.2, C115.2, C116.2, C117.2, C118.2, C119.2, C120.2, C121.2, C122.2, C123.2, C124.2, C125.2, C126.2, R206.2, R207.2, R208.2, R209.2, R216.2, R217.2, R222.2, R223.2, U25.8 (GND); also elsewhere on the board
unnamed: Q33.1 (B), R202.1, R206.1
unnamed: Q33.3 (C), R210.2
unnamed: Q34.1 (B), R203.1, R207.1
unnamed: Q34.3 (C), R211.2
unnamed: Q35.1 (B), R204.1, R208.1
unnamed: Q35.3 (C), R212.2
unnamed: Q36.1 (B), R205.1, R209.1
unnamed: Q36.3 (C), R213.2
unnamed: Q37.1 (B), R214.1, R216.1
unnamed: Q37.3 (C), R218.2
unnamed: Q38.1 (B), R215.1, R217.1
unnamed: Q38.3 (C), R219.2
unnamed: Q39.1 (B), R220.1, R222.1
unnamed: Q39.3 (C), R224.2
unnamed: Q40.1 (B), R221.1, R223.1
unnamed: Q40.3 (C), R225.2

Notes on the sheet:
DIGITAL OUT
STO-OUT

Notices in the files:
parts and their libraries:
Copyright 2016 Accelerated Designs. All rights reserved.
